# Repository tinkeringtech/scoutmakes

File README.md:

**ScoutMakes STEM Electronic Kits**

These are the source design files for the ScoutMakes Electronic Kits
- ScoutMakes FM Kit
- ScoutMakes Robot Kit
- ScoutMakes Azul

The kits can be bought at https://www.scoutmakes.com.
Please support this educational company by buying our products focused on cultivating more engineers!

Designed by TinkeringTech.

Hardware and documentation license: Creative Commons ShareAlike 3.0 United States (CC BY-SA 3.0 US)

Software License: MIT License

Check license.txt for more information.

All text above must be included in any redistribution.

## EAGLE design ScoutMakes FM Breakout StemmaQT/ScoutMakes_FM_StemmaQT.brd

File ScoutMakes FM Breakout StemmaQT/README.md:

**ScoutMakes FM breakout STEMMA QT/QWIIC I2C**

These are the source design files for the ScoutMakes FM Radio Board STEMMA/Qwiic I2C.

The kits can be bought at https://www.scoutmakes.com.
Please support this educational company by buying our products focused on cultivating more engineers!

Designed by TinkeringTech.
License: Creative Commons ShareAlike 3.0 United States (CC BY-SA 3.0 US)
License: MIT License
Check license.txt for more information All text above must be included in any redistribution.

**FM Radio Kit Features & Specifications**
- Open hardware & open source software
- RDA5807M single-chip FM receiver
- High-quality stereo audio output
- Built-in volume and bass control
- Received signal strength indicator (RSSI) information
- Station scanning and presets are supported in code
- Radio Data Service (RDS) information available for display
- Received signal strength (RSSI) indication
- Adafruit CircuitPython library
- Adafruit STEMMA QT and SparkFun Qwiic connectors for easy, solderless attachment of other I²C devices
- 3.5 mm audio jack
- Power LED indicator

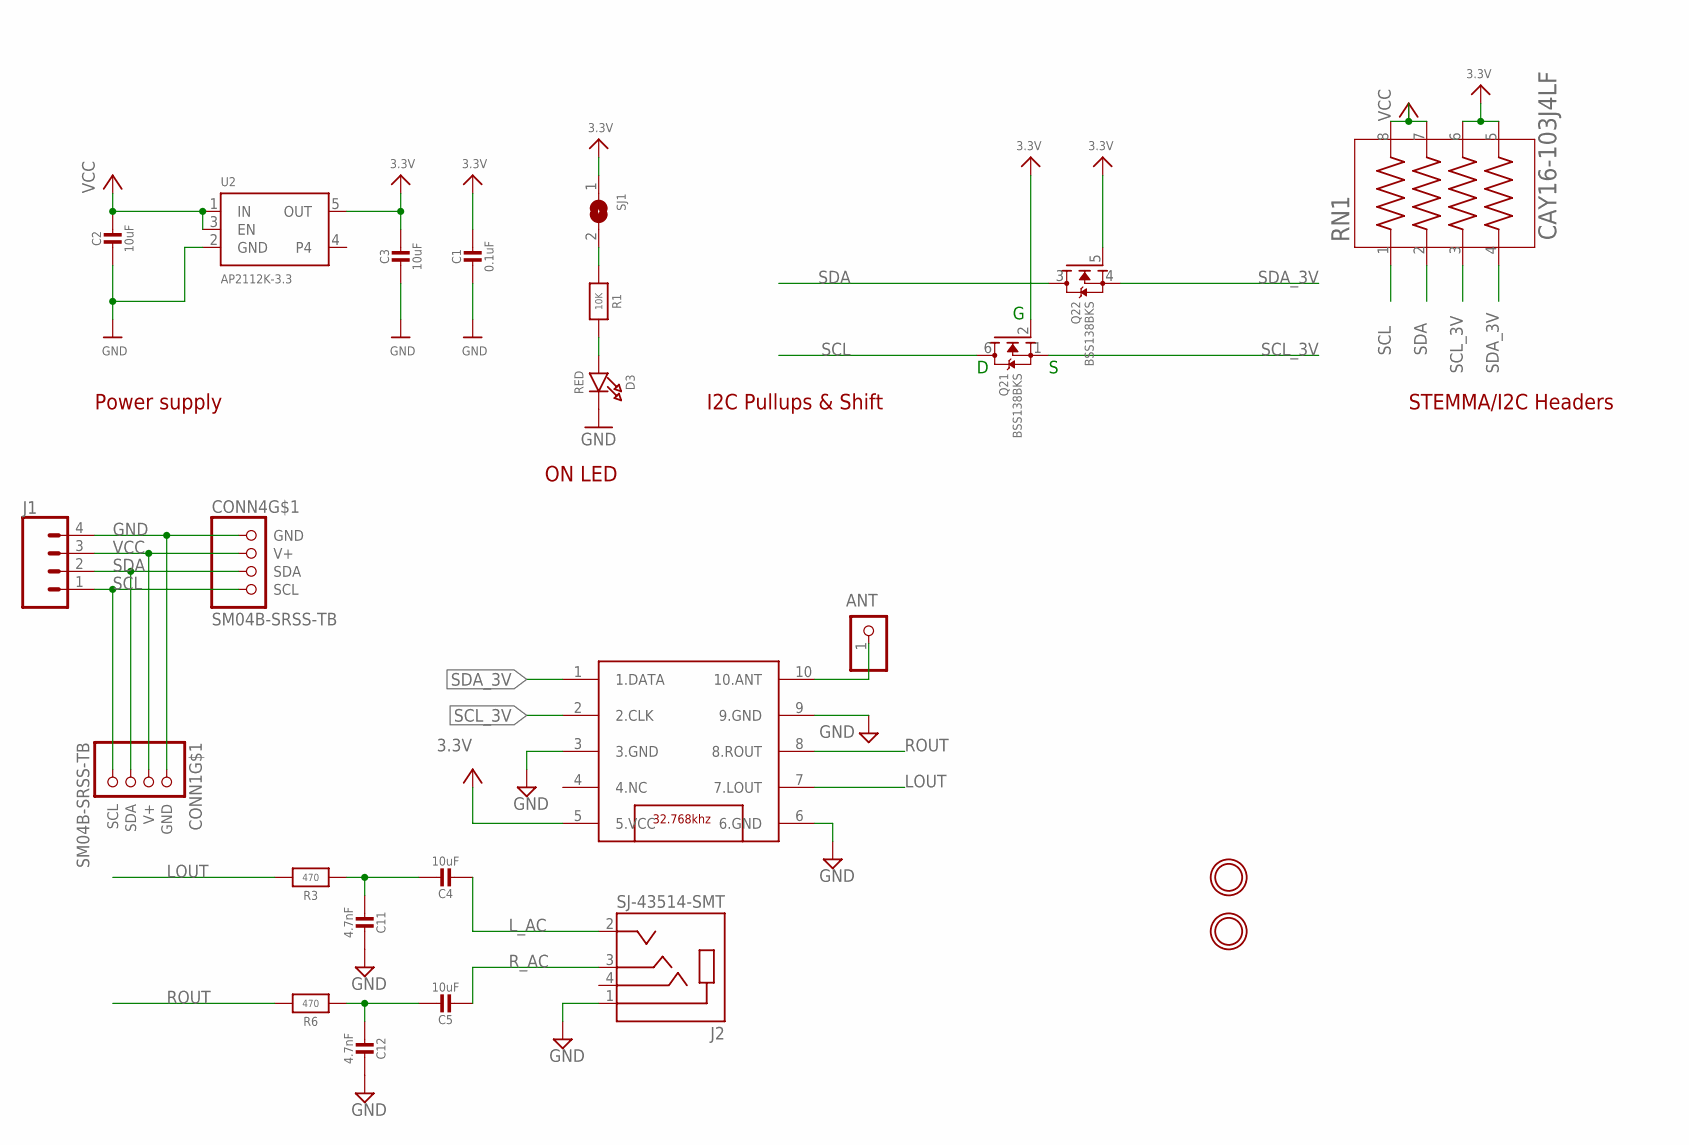
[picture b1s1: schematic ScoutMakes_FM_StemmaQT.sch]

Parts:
ANT: PINHD-1X1; 1X01
C1: 0.1uF; 0603-NO
C2, C3, C4, C5: 10uF; 0805-NO
C11, C12: 4.7nF; 0805-NO
CONN1, CONN4: SM04B-SRSS-TB; JST_SH4
D3: RED; CHIPLED_0805_NOOUTLINE
J1: CONN_04; 1X04
J2: SJ-43514-SMT; CUI_SJ-43514-SMT
Q2: BSS138BKS; SOT363
R1: 10K; 0603-NO
R3, R6: 470; 0805-NO
RN1: CAY16-103J4LF; RESCAF80P320X160X60-8N
SJ1: SOLDERJUMPER; SOLDERJUMPER_ARROW_NOPASTE
U1: TEA5767; TJ-102BC
U2: AP2112K-3.3; SOT23-5
U$1, U$17: MOUNTINGHOLE2.5; MOUNTINGHOLE_2.5_PLATED

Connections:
3.3V: C1.1, C3.1, Q2.2 (G), Q2.5 (G), RN1.5, RN1.6, SJ1.1, U1.5 (5.VCC), U2.5 (OUT)
ANT: ANT.1, U1.10 (10.ANT)
GND: C1.2, C2.2, C3.2, C11.2, C12.2, CONN1.1 (GND), CONN4.1 (GND), D3.C, J1.4, J2.1 (SLEEVE), U1.3 (3.GND), U1.6 (6.GND), U1.9 (9.GND), U2.2 (GND)
LOUT: R3.1, U1.7 (7.LOUT)
L_AC: C4.1, J2.2 (TIP)
unnamed: D3.A, R1.2
unnamed: C5.2, C12.1, R6.2
unnamed: R1.1, SJ1.2
unnamed: C4.2, C11.1, R3.2
ROUT: R6.1, U1.8 (8.ROUT)
R_AC: C5.1, J2.3 (RING1)
SCL: CONN1.4 (SCL), CONN4.4 (SCL), J1.1, Q2.6 (D), RN1.1
SCL_3V: Q2.1 (S), RN1.3, U1.2 (2.CLK)
SDA: CONN1.3 (SDA), CONN4.3 (SDA), J1.2, Q2.3 (D), RN1.2
SDA_3V: Q2.4 (S), RN1.4, U1.1 (1.DATA)
VCC: C2.1, CONN1.2 (V+), CONN4.2 (V+), J1.3, RN1.7, RN1.8, U2.1 (IN), U2.3 (EN)

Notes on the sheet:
I2C Pullups & Shift
STEMMA/I2C Headers
ON LED
Power supply

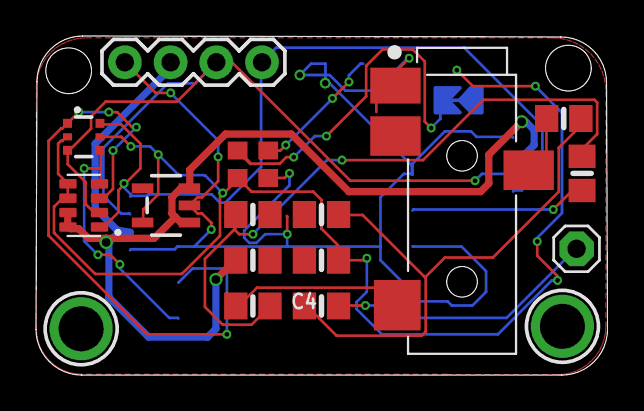
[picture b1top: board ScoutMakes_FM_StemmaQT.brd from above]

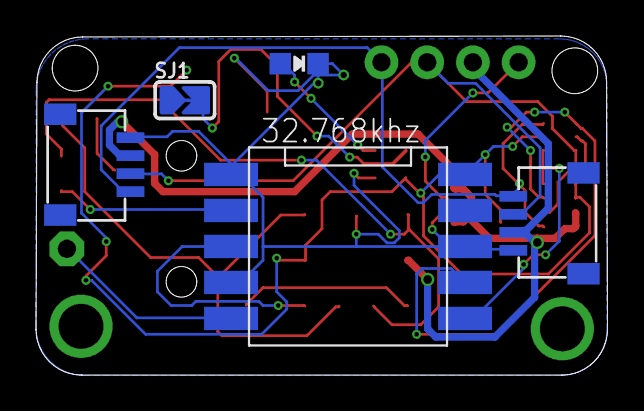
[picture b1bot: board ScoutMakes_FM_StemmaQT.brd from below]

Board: 2 copper layers, 31.8 x 18.8 mm, 23 parts (5 on the bottom side), 16 nets.

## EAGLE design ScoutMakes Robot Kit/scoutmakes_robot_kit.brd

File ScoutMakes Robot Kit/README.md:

**ScoutMakes Robot STEM Electronic Kits**

**Open Source Hardware Association certified OSHWA UID US000676**

These are the source design files for the ScoutMakes Robot Electronic Kit.

The kits can be bought at https://www.scoutmakes.com.
Please support this eduactiional company by buying our products focused on cultivating more engineers!

The Chassis 3D print TinkerCad files can be found at https://www.tinkercad.com/things/9izqkyQWX8r

Designed by TinkeringTech.
License: Creative Commons ShareAlike 3.0 United States (CC BY-SA 3.0 US)
License: MIT License
Check license.txt for more information All text above must be included in any redistribution.

**Robot Kit Features & Specifications**
- Open hardware and open source software
- Quick and easy assembly (all mechanical hardware is included in the kit)
- Controllable over BLE using an iOS or Android app
- A piezoelectric speaker allows your robot to make sounds
- Powered by a rechargeable, LiPo battery
- Four NeoPixels on the robot board provide illumination
- Modify the source files for the robot chassis and 3D print your own designs
- Quality, N20 motors with metal gear boxes and rubber tires

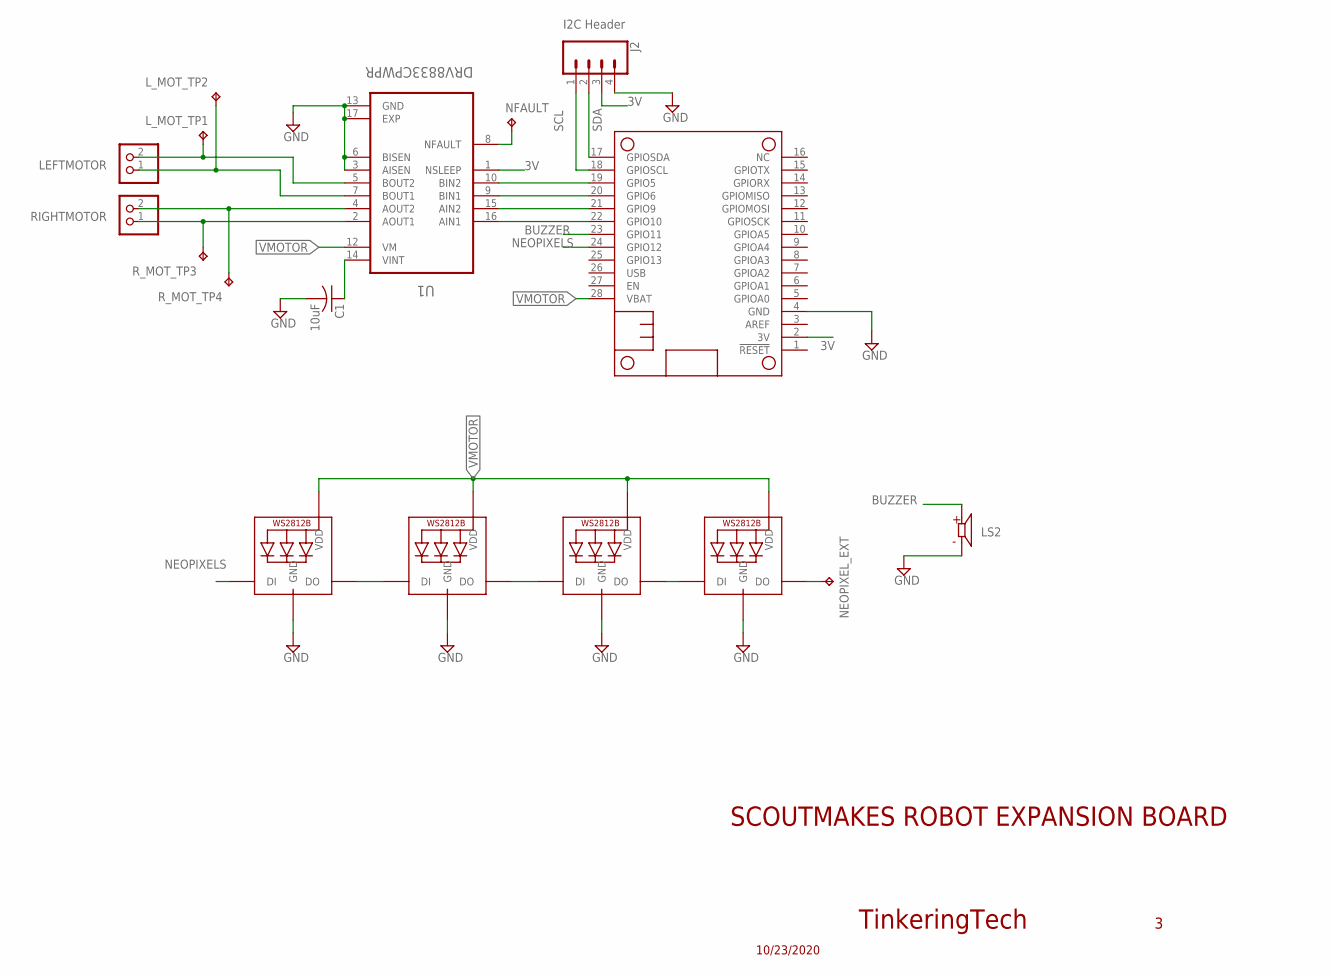
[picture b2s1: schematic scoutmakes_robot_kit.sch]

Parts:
C1: 10uF; C0805
J2: CONN_04; 1X04
LED1, LED2, LED3, LED4: WS2812B_4020
LEFTMOTOR: JSTPH; JSTPH2
LS2: PKMCS0909E4000-R1; SPKR_PKMCS0909E4000-R1
L_MOT_TP1, L_MOT_TP2: TPTP09R; TP09R
MS2: FEATHERWING_NODIM; FEATHERWING_DIM
NEOPIXEL_EXT: TPTP09R; TP09R
NFAULT: TPTP09R; TP09R
RIGHTMOTOR: JSTPH; JSTPH2
R_MOT_TP3, R_MOT_TP4: TPTP09R; TP09R
U1: DRV8833CPWPR; SOP65P640X120-17N

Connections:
3V: J2.3, MS2.2 (3V), U1.1 (NSLEEP)
BUZZER: LS2.1, MS2.23 (GPIO11)
GND: C1.2, J2.4, LED1.4 (GND), LED2.4 (GND), LED3.4 (GND), LED4.4 (GND), LS2.2 (N), MS2.4 (GND), U1.3 (AISEN), U1.6 (BISEN), U1.13 (GND), U1.17 (EXP)
unnamed: RIGHTMOTOR.2, R_MOT_TP4.TP, U1.4 (AOUT2)
unnamed: RIGHTMOTOR.1, R_MOT_TP3.TP, U1.2 (AOUT1)
unnamed: LEFTMOTOR.1, L_MOT_TP2.TP, U1.7 (BOUT1)
unnamed: LEFTMOTOR.2, L_MOT_TP1.TP, U1.5 (BOUT2)
unnamed: MS2.19 (GPIO5), U1.10 (BIN2)
unnamed: MS2.20 (GPIO6), U1.9 (BIN1)
unnamed: MS2.21 (GPIO9), U1.15 (AIN2)
unnamed: MS2.22 (GPIO10), U1.16 (AIN1)
unnamed: NFAULT.TP, U1.8 (NFAULT)
unnamed: C1.1, U1.14 (VINT)
unnamed: LED1.3 (DO), LED2.1 (DI)
unnamed: LED2.3 (DO), LED3.1 (DI)
unnamed: LED3.3 (DO), LED4.1 (DI)
unnamed: LED4.3 (DO), NEOPIXEL_EXT.TP
NEOPIXELS: LED1.1 (DI), MS2.24 (GPIO12)
SCL: J2.1, MS2.18 (GPIOSCL)
SDA: J2.2, MS2.17 (GPIOSDA)
VMOTOR: LED1.2 (VDD), LED2.2 (VDD), LED3.2 (VDD), LED4.2 (VDD), MS2.28 (VBAT), U1.12 (VM)

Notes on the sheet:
SCOUTMAKES ROBOT EXPANSION BOARD
10/23/2020
TinkeringTech
I2C Header

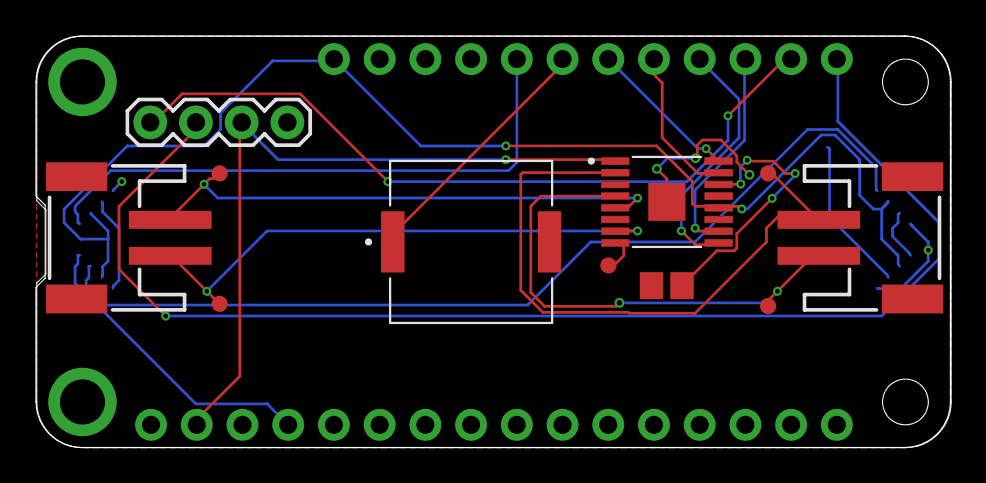
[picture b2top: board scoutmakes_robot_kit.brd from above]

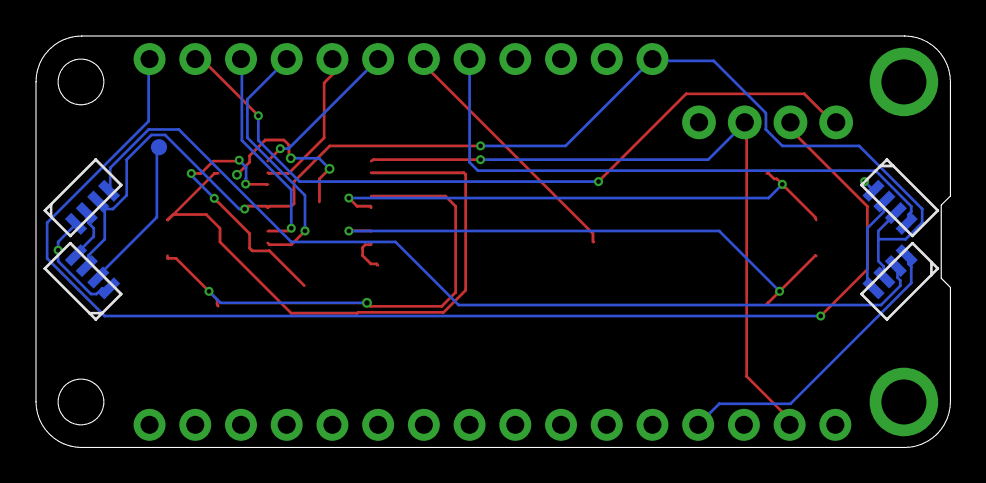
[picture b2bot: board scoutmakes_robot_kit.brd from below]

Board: 2 copper layers, 50.8 x 22.9 mm, 17 parts (5 on the bottom side), 21 nets.

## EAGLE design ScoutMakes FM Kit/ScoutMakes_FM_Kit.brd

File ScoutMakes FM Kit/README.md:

**ScoutMakes FM radio STEM Electronic Kit**

**Open Source Hardware Association certified OSHWA UID US000675**

These are the source design files for the ScoutMakes FM radio Electronic Kit.

The kits can be bought at https://www.scoutmakes.com.
Please support this educational company by buying our products focused on cultivating more engineers!

Designed by TinkeringTech.
License: Creative Commons ShareAlike 3.0 United States (CC BY-SA 3.0 US)
License: MIT License
Check license.txt for more information All text above must be included in any redistribution.

**FM Radio Kit Features & Specifications**
- Open hardware & open source software
- RDA5807M single-chip FM receiver
- Controllable over BLE using an iOS or Android app
- Portable and powered by a rechargeable, LiPo battery
- High-quality stereo audio output
- Built-in volume and bass control
- Received signal strength indicator (RSSI) information
- Station scanning and presets are supported in code
- Radio Data Service (RDS) information available for display
- Received signal strength (RSSI) indication
- Adafruit CircuitPython library
- Adafruit STEMMA QT and SparkFun Qwiic connectors for easy, solderless attachment of other I²C devices
- User-assignable push-buttons for control
- 3.5 mm audio jack

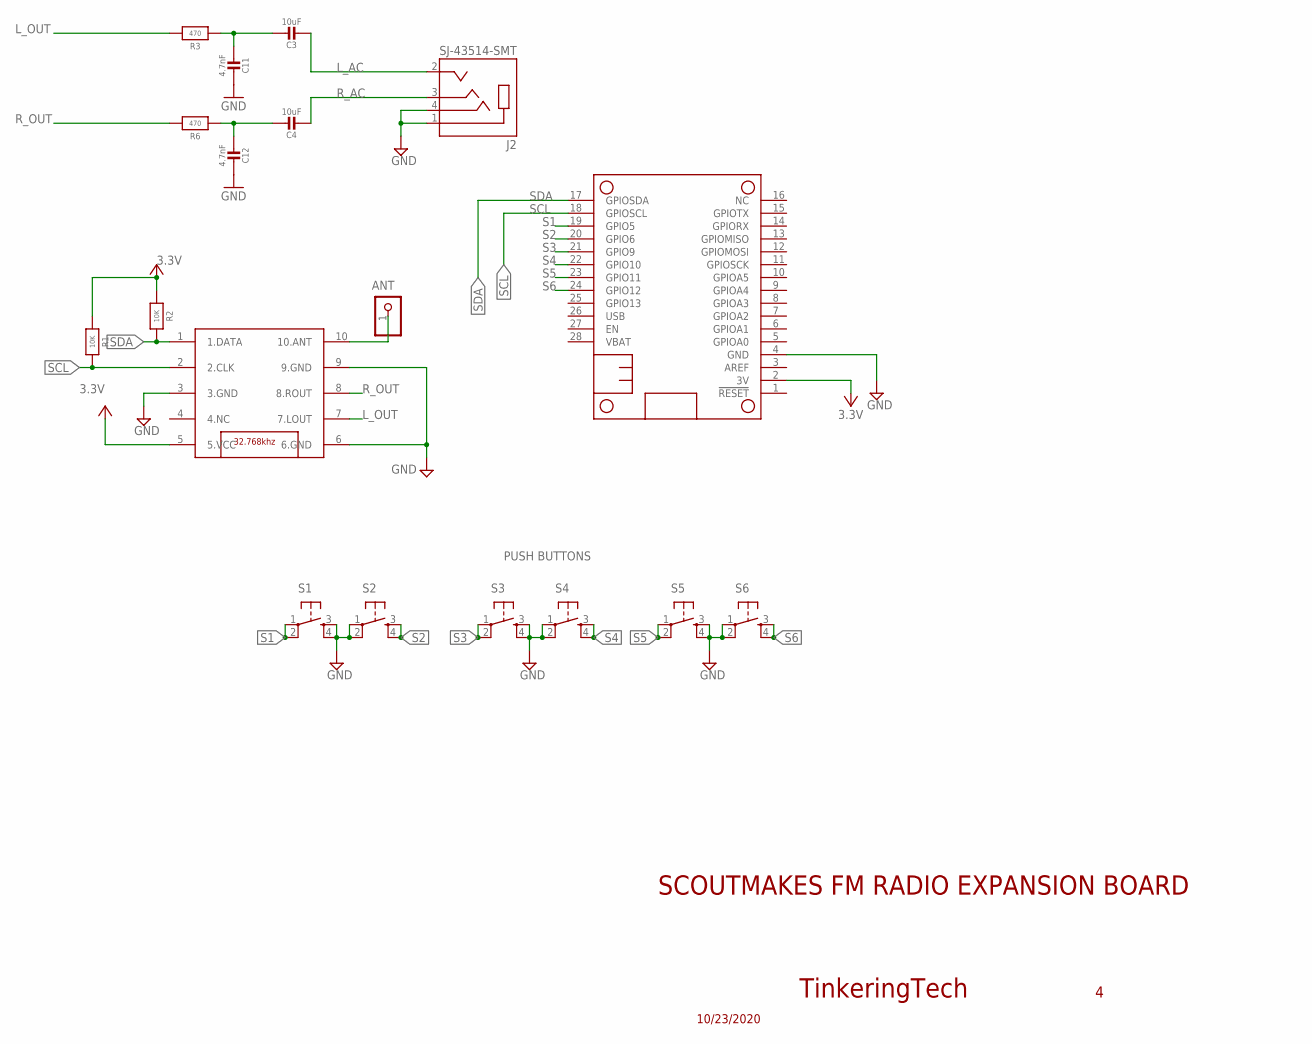
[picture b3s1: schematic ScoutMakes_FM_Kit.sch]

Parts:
ANT: PINHD-1X1; 1X01
C3, C4: 10uF; 0805-NO
C11, C12: 4.7nF; 0805-NO
J2: SJ-43514-SMT; CUI_SJ-43514-SMT
MS2: FEATHERWING_NODIM; FEATHERWING_DIM
R1, R2: 10K; 0603-NO
R3, R6: 470; 0805-NO
S1, S2, S3, S4, S5, S6: DTS-6
U1: TEA5767; TJ-102BC

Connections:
3.3V: MS2.2 (3V), R1.1, R2.1, U1.5 (5.VCC)
ANT: ANT.1, U1.10 (10.ANT)
GND: C11.2, C12.2, J2.1 (SLEEVE), J2.4 (RING2), MS2.4 (GND), S1.3, S1.4, S2.1, S2.2, S3.3, S3.4, S4.1, S4.2, S5.3, S5.4, S6.1, S6.2, U1.3 (3.GND), U1.6 (6.GND), U1.9 (9.GND)
L_AC: C3.1, J2.2 (TIP)
L_OUT: R3.1, U1.7 (7.LOUT)
unnamed: C4.2, C12.1, R6.2
unnamed: C3.2, C11.1, R3.2
R_AC: C4.1, J2.3 (RING1)
R_OUT: R6.1, U1.8 (8.ROUT)
S1: MS2.19 (GPIO5), S1.1, S1.2
S2: MS2.20 (GPIO6), S2.3, S2.4
S3: MS2.21 (GPIO9), S3.1, S3.2
S4: MS2.22 (GPIO10), S4.3, S4.4
S5: MS2.23 (GPIO11), S5.1, S5.2
S6: MS2.24 (GPIO12), S6.3, S6.4
SCL: MS2.18 (GPIOSCL), R1.2, U1.2 (2.CLK)
SDA: MS2.17 (GPIOSDA), R2.2, U1.1 (1.DATA)

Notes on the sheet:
SCOUTMAKES FM RADIO EXPANSION BOARD
10/23/2020
TinkeringTech
PUSH BUTTONS

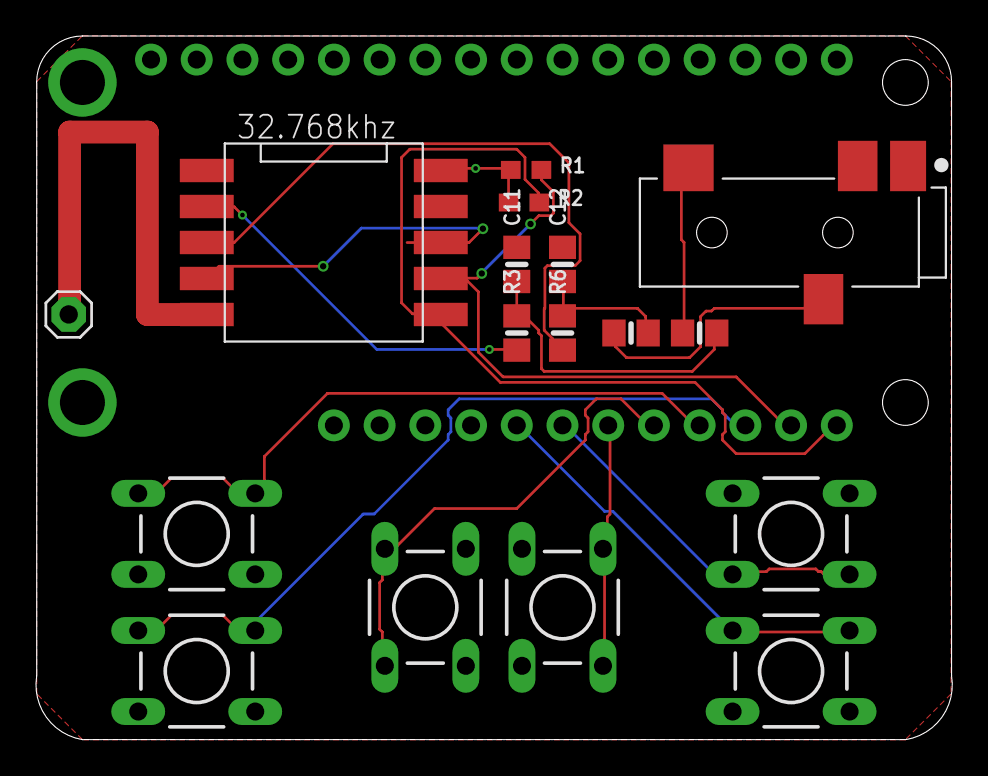
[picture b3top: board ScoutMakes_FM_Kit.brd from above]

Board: 2 copper layers, 50.9 x 39.1 mm, 18 parts (1 on the bottom side), 17 nets.

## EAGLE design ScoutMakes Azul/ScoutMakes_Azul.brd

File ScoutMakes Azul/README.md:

**ScoutMakes Azul Bluetooth BLE STEM Electronic Kit**

**Open Source Hardware Association certified OSHWA UID US000652**

These are the source design files for the ScoutMakes Azul Bluetooth BLE Electronic Kit.

The kits can be bought at https://www.scoutmakes.com or https://www.tindie.com/products/tinkeringtech/scoutmakes-azul-nrf52840-bluetooth-maker-platform/

Please support this eduactiional company by buying our products focused on cultivating more engineers!

Designed by TinkeringTech.

Hardware and documentation license: Creative Commons ShareAlike 3.0 United States (CC BY-SA 3.0 US)

Software License: MIT License

Check license.txt for more information.

All text above must be included in any redistribution.

Features:

- ARM Cortex M4F (with HW floating point acceleration) running at 64MHz
- Raytac MDBT50Q-1MV2 BLE module. FCC / IC / TELEC certified module
- 1MB flash and 256KB SRAM
- Native Open Source USB stack – pre-programmed with UF2 bootloader and CircuitPython
- 128×32 OLED display
- USB type-C
- On/off power switch
- Bluetooth Low Energy compatible 2.4GHz radio (Details available in the nRF52840 product specification)
- BT5.1 & BT5 Bluetooth Specification Certified
- Supports BT5 Long Range Feature
- 1.7v to 3.3v operation with internal linear and DC/DC voltage regulators
- 21 GPIO, 6 x 12-bit ADC pins, up to 12 PWM outputs (3 PWM modules with 4 outputs each)
- Pin #3 red LED for general purpose blinking,
- Programmable NeoPixel for colorful feedback = 4 mounting holes
- Reset button
- Works out of the box with Adafruit feather wings.

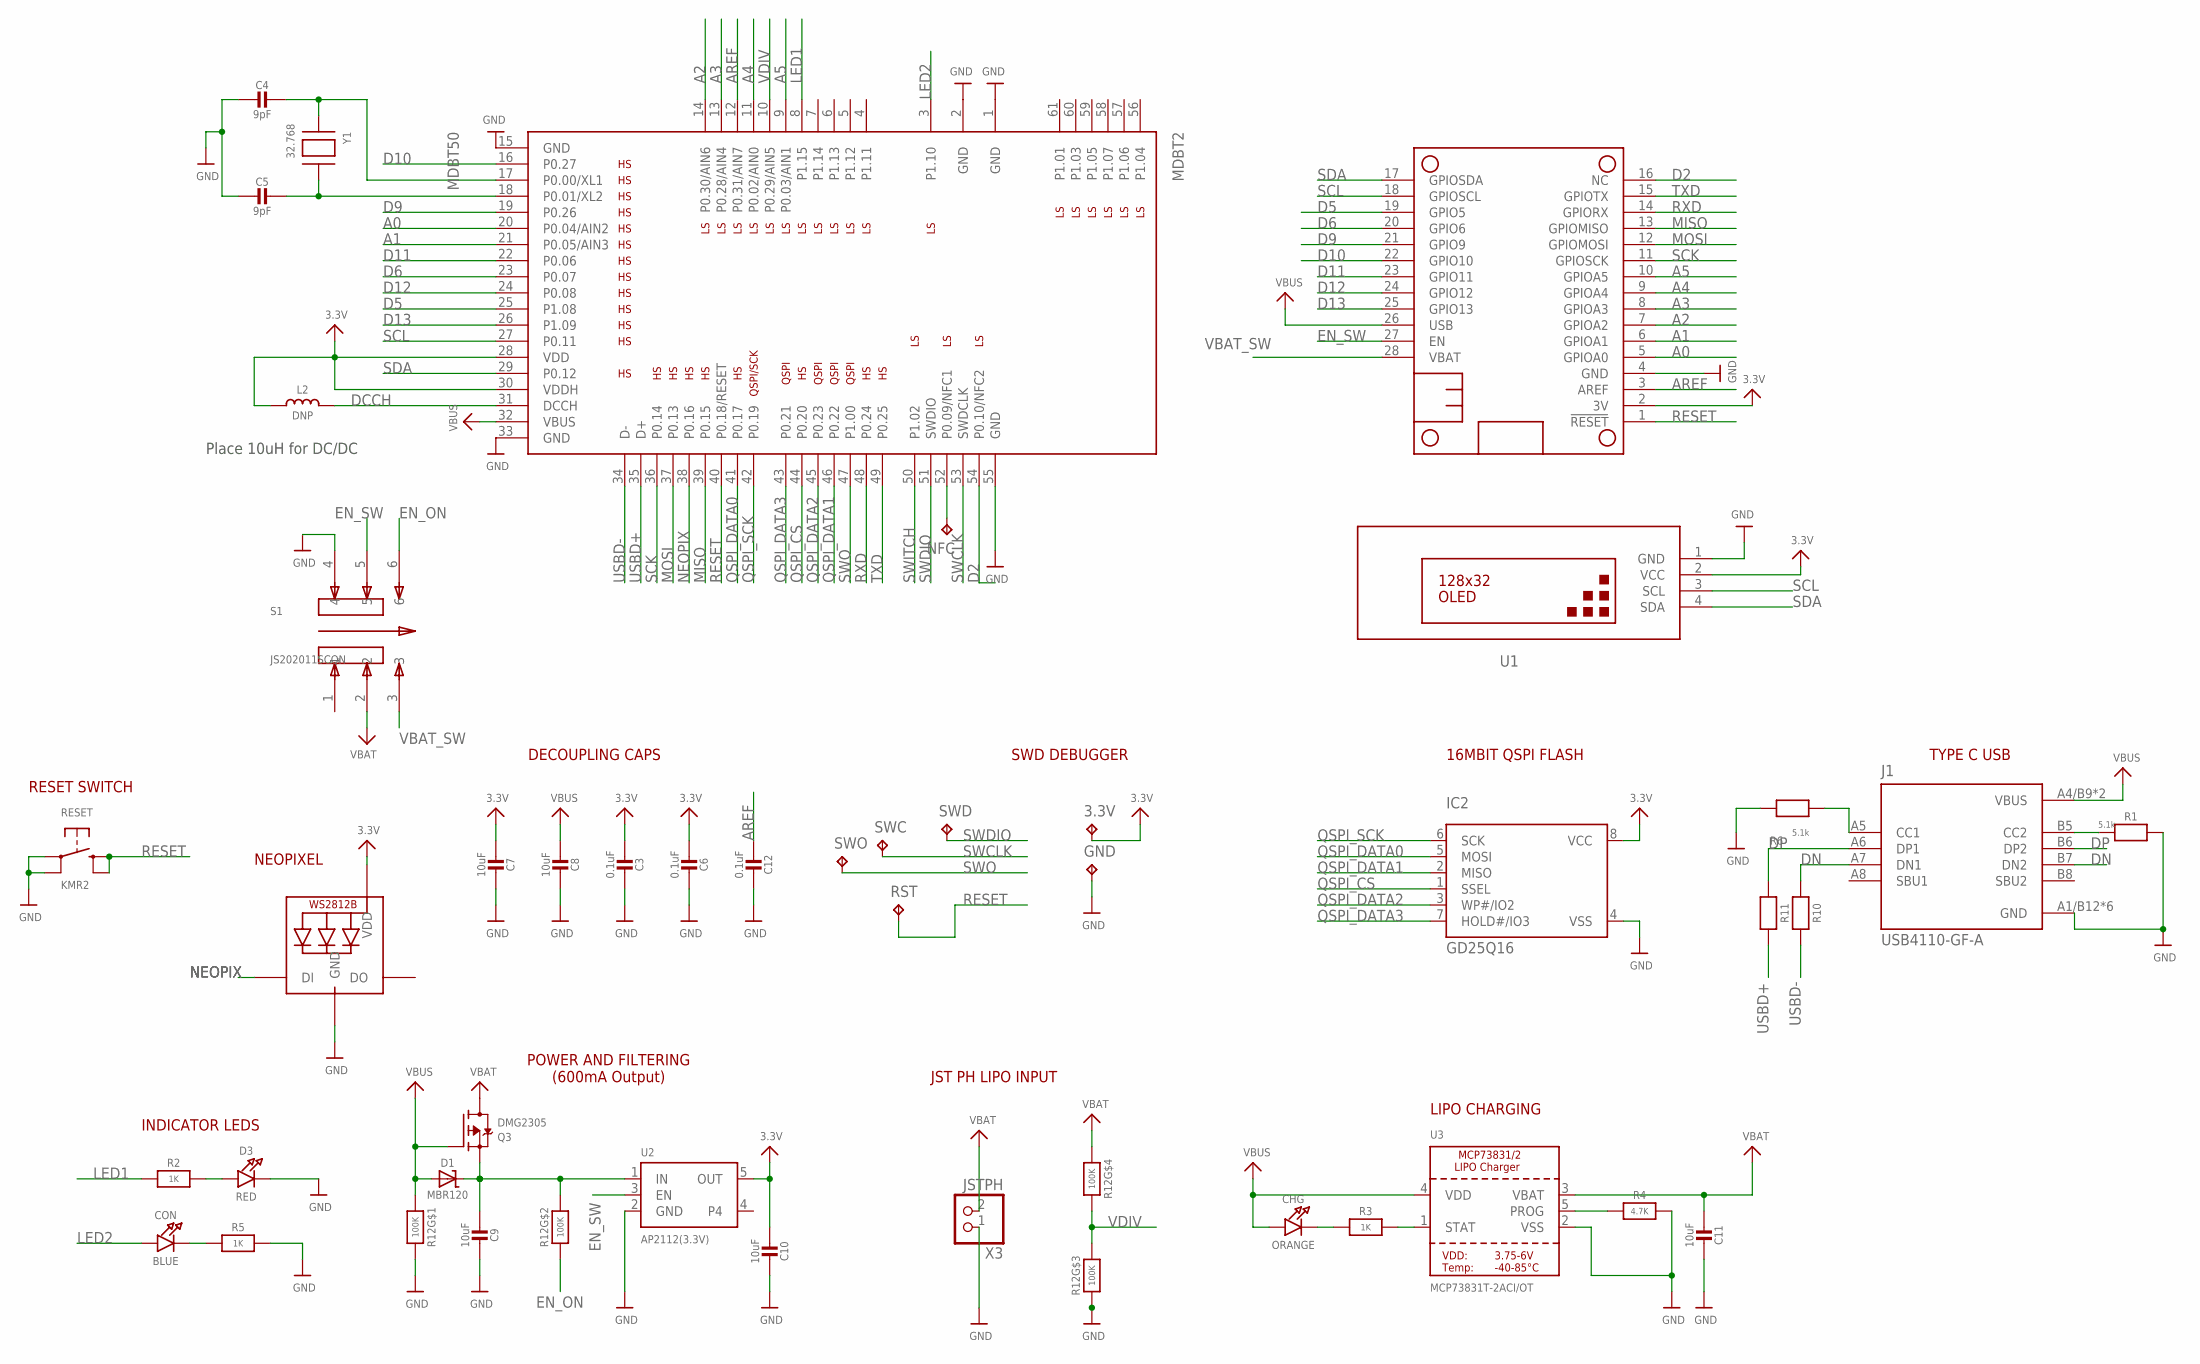
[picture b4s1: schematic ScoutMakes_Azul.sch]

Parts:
3.3V: TPTP12R; TP12R
C3, C6, C12: 0.1uF; 0603-NO
C4, C5: 9pF; 0603-NO
C7, C8, C9, C10, C11: 10uF; 0805-NO
CHG: ORANGE; CHIPLED_0805_NOOUTLINE
CON: BLUE; CHIPLED_0805_NOOUTLINE
D1: MBR120; SOD-123
D3: RED; CHIPLED_0805_NOOUTLINE
GND: TPTP12R; TP12R
IC2: GD25Q16; USON8
J1: USB4110-GF-A; GCT_USB4110-GF-A
L2: DNP; _0805MP
LED: WS2812B3535; LED3535
MDBT2: MDBT50
MS1: FEATHERWING_NODIM
NFC: TPTP10R; TP10R
Q3: DMG2305; SOT23-R
R1, R6: 5.1k; 0603-NO
R2, R3, R5: 1K; 0603-NO
R4: 4.7K; 0603-NO
R10, R11: 22; 0603-NO
R12: 100K; RESPACK_4X0603
RESET: KMR2; BTN_KMR2_4.6X2.8
RST: TPTP12R; TP12R
S1: JS202011SCQN; SW_JS202011SCQN
SWC: TPTP12R; TP12R
SWD: TPTP12R; TP12R
SWO: TPTP12R; TP12R
U1: DISPLAY-OLED-128X32
U2: AP2112(3.3V); SOT23-5
U3: MCP73831T-2ACI/OT; SOT23-5
X3: JSTPH; JSTPH2
Y1: 32.768; XTAL3215

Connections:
3.3V: 3.3V.TP, C3.2, C6.2, C7.2, C10.2, IC2.8 (VCC), L2.1, LED.2 (VDD), MDBT2.28 (VDD), MDBT2.30 (VDDH), MS1.2 (3V), U1.2 (VCC), U2.5 (OUT)
A0: MDBT2.20 (P0.04/AIN2), MS1.5 (GPIOA0)
A1: MDBT2.21 (P0.05/AIN3), MS1.6 (GPIOA1)
A2: MDBT2.14 (P0.30/AIN6), MS1.7 (GPIOA2)
A3: MDBT2.13 (P0.28/AIN4), MS1.8 (GPIOA3)
A4: MDBT2.11 (P0.02/AIN0), MS1.9 (GPIOA4)
A5: MDBT2.9 (P0.03/AIN1), MS1.10 (GPIOA5)
AREF: C12.2, MDBT2.12 (P0.31/AIN7), MS1.3 (AREF)
D2: MDBT2.54 (P0.10/NFC2), MS1.16 (NC)
D5: MDBT2.25 (P1.08), MS1.19 (GPIO5)
D6: MDBT2.23 (P0.07), MS1.20 (GPIO6)
D9: MDBT2.19 (P0.26), MS1.21 (GPIO9)
D10: MDBT2.16 (P0.27), MS1.22 (GPIO10)
D11: MDBT2.22 (P0.06), MS1.23 (GPIO11)
D12: MDBT2.24 (P0.08), MS1.24 (GPIO12)
D13: MDBT2.26 (P1.09), MS1.25 (GPIO13)
DCCH: L2.2, MDBT2.31 (DCCH)
DN: J1.A7 (DN1), J1.B7 (DN2), R10.1
DP: J1.A6 (DP1), J1.B6 (DP2), R11.1
EN_ON: R12.2 (1), S1.6
EN_SW: MS1.27 (EN), S1.5, U2.3 (EN)
GND: C3.1, C4.2, C5.2, C6.1, C7.1, C8.1, C9.1, C10.1, C11.1, C12.1, D3.C, GND.TP, IC2.4 (VSS), J1.A1/B12 (GND), J1.B1/A12 (GND), J1.S1 (GND), J1.S2 (GND), J1.S3 (GND), J1.S4 (GND), LED.4 (GND), MDBT2.1 (GND), MDBT2.2 (GND), MDBT2.15 (GND), MDBT2.33 (GND), MDBT2.55 (GND), MS1.4 (GND), R1.2, R4.2, R5.2, R6.2, R12.3 (1), R12.8 (2), RESET.A, RESET.A' (P1), S1.4, U1.1 (GND), U2.2 (GND), U3.2 (VSS), X3.1
LED1: MDBT2.8 (P1.15), R2.1
LED2: CON.A, MDBT2.3 (P1.10)
MISO: MDBT2.39 (P0.15), MS1.13 (GPIOMISO)
MOSI: MDBT2.37 (P0.13), MS1.12 (GPIOMOSI)
unnamed: C4.1, MDBT2.17 (P0.00/XL1), Y1.P$1
unnamed: C5.1, MDBT2.18 (P0.01/XL2), Y1.P$2
unnamed: CHG.C, R3.1
unnamed: J1.A5 (CC1), R6.1
unnamed: D3.A, R2.2
unnamed: J1.B5 (CC2), R1.1
unnamed: R3.2, U3.1 (STAT)
unnamed: R4.1, U3.5 (PROG)
unnamed: CON.C, R5.1
NEOPIX: LED.1 (DI), MDBT2.38 (P0.16)
NFC1: MDBT2.52 (P0.09/NFC1), NFC.TP
QSPI_CS: IC2.1 (SSEL), MDBT2.44 (P0.20)
QSPI_DATA0: IC2.5 (MOSI), MDBT2.41 (P0.17)
QSPI_DATA1: IC2.2 (MISO), MDBT2.46 (P0.22)
QSPI_DATA2: IC2.3 (WP#/IO2), MDBT2.45 (P0.23)
QSPI_DATA3: IC2.7 (HOLD#/IO3), MDBT2.43 (P0.21)
QSPI_SCK: IC2.6 (SCK), MDBT2.42 (P0.19)
RESET: MDBT2.40 (P0.18/RESET), MS1.1 (!RESET), RESET.B (S), RESET.B' (S1), RST.TP
RXD: MDBT2.48 (P0.24), MS1.14 (GPIORX)
SCK: MDBT2.36 (P0.14), MS1.11 (GPIOSCK)
SCL: MDBT2.27 (P0.11), MS1.18 (GPIOSCL), U1.3 (SCL)
SDA: MDBT2.29 (P0.12), MS1.17 (GPIOSDA), U1.4 (SDA)
SWCLK: MDBT2.53 (SWDCLK), SWC.TP
SWDIO: MDBT2.51 (SWDIO), SWD.TP
SWITCH: MDBT2.50 (P1.02)
SWO: MDBT2.47 (P1.00), SWO.TP
TXD: MDBT2.49 (P0.25), MS1.15 (GPIOTX)
USBD+: MDBT2.35 (D+), R11.2
USBD-: MDBT2.34 (D-), R10.2
VBAT: C11.2, Q3.3 (D), R12.4 (1), S1.2, U3.3 (VBAT), X3.2
VBAT_SW: MS1.28 (VBAT), S1.3
VBUS: C8.2, CHG.A, D1.A, J1.A4/B9 (VBUS), J1.B4/A9 (VBUS), MDBT2.32 (VBUS), MS1.26 (USB), Q3.1 (G), R12.1, U3.4 (VDD)
VDIV: MDBT2.10 (P0.29/AIN5), R12.5 (2), R12.6 (2)
VHI: C9.2, D1.C, Q3.2 (S), R12.7 (2), U2.1 (IN)

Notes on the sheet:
LIPO CHARGING
POWER AND FILTERING (600mA Output)
JST PH LIPO INPUT
INDICATOR LEDS
RESET SWITCH
DECOUPLING CAPS
SWD DEBUGGER
16MBIT QSPI FLASH
TYPE C USB
Place 10uH for DC/DC
NEOPIXEL

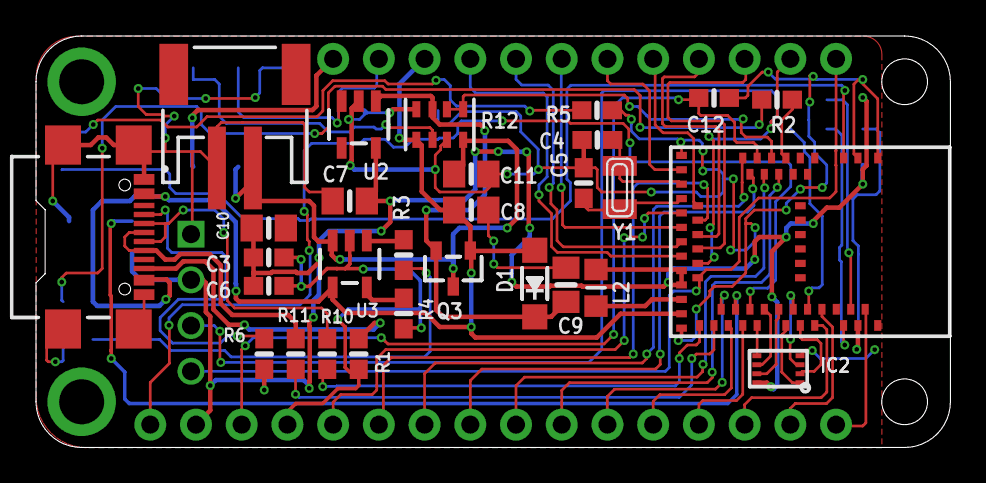
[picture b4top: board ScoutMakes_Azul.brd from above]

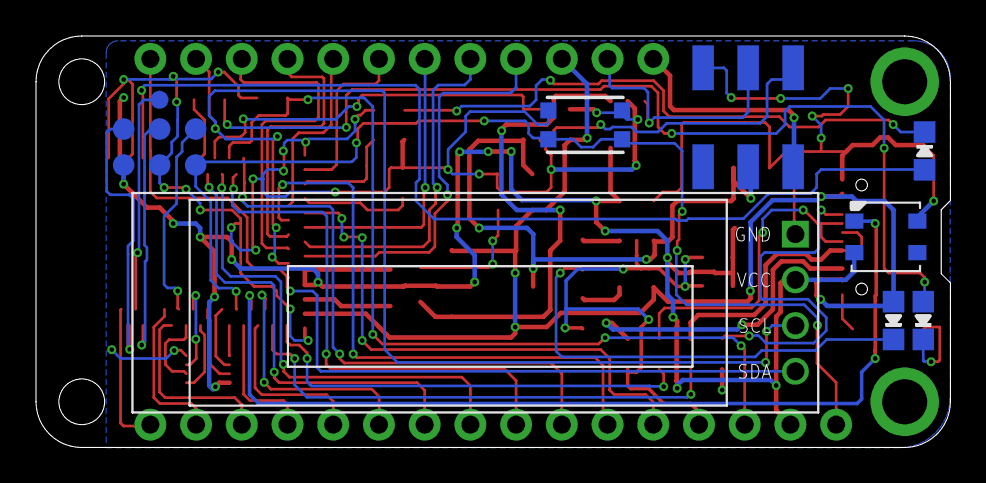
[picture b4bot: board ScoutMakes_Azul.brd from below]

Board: 2 copper layers, 50.8 x 22.9 mm, 44 parts (14 on the bottom side), 59 nets.

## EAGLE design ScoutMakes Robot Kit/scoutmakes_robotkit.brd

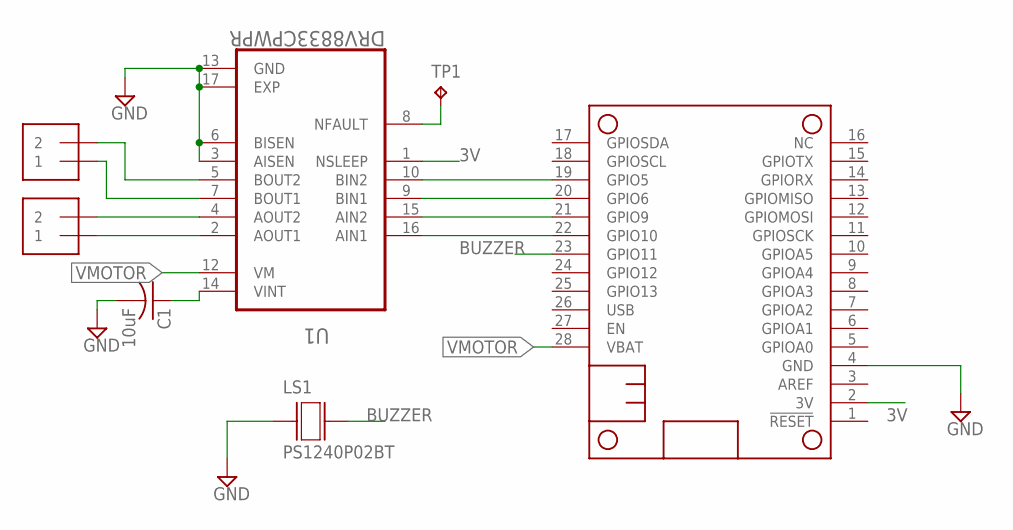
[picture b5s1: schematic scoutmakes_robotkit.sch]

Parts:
C1: 10uF; C0805
J1, J2: 1X2-3.5MM
LS1: PS1240P02BT; XDCR_PS1240P02BT
MS2: FEATHERWING_NODIM; FEATHERWING_DIM
TP1: TPTP09R; TP09R
U1: DRV8833CPWPR; SOP65P640X120-17N

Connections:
3V: MS2.2 (3V), U1.1 (NSLEEP)
BUZZER: LS1.2, MS2.23 (GPIO11)
GND: C1.2, LS1.1, MS2.4 (GND), U1.3 (AISEN), U1.6 (BISEN), U1.13 (GND), U1.17 (EXP)
unnamed: J2.1, U1.2 (AOUT1)
unnamed: J2.2, U1.4 (AOUT2)
unnamed: J1.1, U1.7 (BOUT1)
unnamed: J1.2, U1.5 (BOUT2)
unnamed: MS2.19 (GPIO5), U1.10 (BIN2)
unnamed: MS2.20 (GPIO6), U1.9 (BIN1)
unnamed: MS2.21 (GPIO9), U1.15 (AIN2)
unnamed: MS2.22 (GPIO10), U1.16 (AIN1)
unnamed: TP1.TP, U1.8 (NFAULT)
unnamed: C1.1, U1.14 (VINT)
VMOTOR: MS2.28 (VBAT), U1.12 (VM)

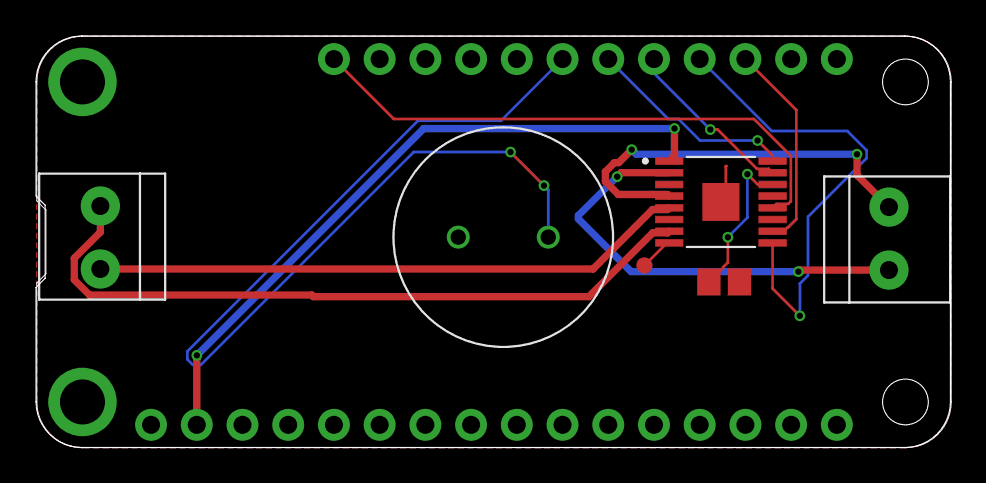
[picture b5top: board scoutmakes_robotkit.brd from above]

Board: 2 copper layers, 50.8 x 22.9 mm, 7 parts (0 on the bottom side), 14 nets.

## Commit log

2020-10-04 Added Azul board files
    Azul V4 files
2020-10-04 Updated board files & added exmaple circuitpython code
2020-10-05 Added assets dir and pictures
2020-10-30 Updated board files
2020-10-30 Added new FM kit pictures
2020-10-30 Added new pictures
2020-10-30 Added new kit combo picture
2020-10-30 Update combo picture
2020-10-30 added new combo picture
2020-10-31 Added new board files
2020-10-31 Include picture in readme
2021-02-23 Latest code updated
2021-03-27 Added 3D print files
2021-03-28 Create TinkerCad 3D print project
2021-05-06 Updated lib files
2021-05-06 Updated FM radio demo files
2022-11-28 Added FM board StemmaQT files
2022-12-03 Add files via upload
    Added examples with Arduino

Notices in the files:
parts and their libraries:
microbuilder: This work is placed in the public domain, and may be freely used for commercial and non-commercial work with the following conditions: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
diy-modules: Released under the Creative Commons Attribution 4.0 International License: http://creativecommons.org/licenses/by/4.0
